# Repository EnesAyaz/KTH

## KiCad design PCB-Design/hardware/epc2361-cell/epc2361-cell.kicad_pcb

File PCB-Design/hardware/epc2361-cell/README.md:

# EPC2361 one-pair placement prototype

Open `epc2361-cell.kicad_pro` in KiCad 7. This is a native schematic and partially routed PCB placement study, not a fabrication release.

## Design basis

- One EPC2361 high-side device and one low-side device; eventual module has six of each.
- Bus: 75 V nominal and maximum. Switching: 50 kHz nominal, 100 kHz maximum.
- Eventual module: 220 A RMS AC. Ideal equal sharing gives 36.7 A RMS per cell and 51.9 A peak for a sinusoid. These are design targets, not demonstrated ratings.
- Study outline: 30 x 40 mm, four copper layers. Fabricator stackup and dielectric spacing are not selected.
- Four 1210 local ceramic sites. Candidate: TDK C3225X7R2A225K230AB, 2.2 uF / 100 V X7R each, 8.8 uF nominal total. Capacitance retained at 75 V, ripple heating and required count remain unqualified. External bulk DC link is needed.

## Placement and interfaces

QH1 and QL1 form a vertical pair, with local capacitors on the right and gate/source contacts on the left. Top copper combs connect the interleaved device pads; the filled first-inner DC-minus plane provides the proposed return path. Loop inductance has not been extracted or measured. The present narrow power traces illustrate topology and are not rated for the target current.

JGH1/JGL1: pin 1 gate input through RG1/RG2; pin 2 local source return. The source trace takes off at the source land nearest the gate. These are exposed contact pads, not a selected connector. The future driver board must preserve short gate/source paths. RG values are provisional; optional RGS1/RGS2 are DNP.

JDC1 = DC+, JDC2 = DC-, JAC1 = AC. Their 3 mm pads reserve interface positions; they are not rated sockets or final high-current terminals.

TP1 = high-side gate; TP2 = high-side source/AC; TP3 = low-side gate; TP4 = low-side source/DC-; TP5 = DC+; TP6 = DC-; TP7 = AC. Probe connections are still unrouted.

The drawing-layer rectangle reserves the MOSFET-top cold-plate contact corridor. An electrically insulating thermal interface is necessary between a common plate and the different source potentials. Cold plate, TIM, compression, mounting holes and thermal performance remain to be designed. Tall capacitors are outside the contact corridor, but the full cold-plate assembly has not been clearance checked.

## Verification and remaining work

KiCad successfully exported the schematic and both previews. The automated audit passes all 22 components and 44 pin-to-net assignments against the schematic manifest and PCB; footprint paths are linked to schematic UUIDs. Netlist labels carry KiCad's root-sheet slash prefix, normalized by the audit.

The latest native KiCad PCB DRC reports **0 geometric DRC violations, 13 unconnected items, and 0 footprint errors**. This is not a clean finished-board DRC: power ports, probes and optional gate resistors still need routing. Native schematic ERC has not been run. See `cell-drc.rpt` and `connectivity-check.txt`.

The project-local EPC2361 footprint transcribes the manufacturer's separate copper, mask and stencil geometries from datasheet revision 2.4, pages 11-12. Independent footprint/assembly sign-off is still required before fabrication; DRC does not validate the transcription against the datasheet.

Next engineering steps are footprint sign-off, selecting the stackup and real terminals, completing wide power distribution and probe routing, checking capacitance under bias, and electrothermal/commutation validation. Do not scale this cell by simply copying long shared gate traces. The six-cell board and gate-driver PCB are deferred.

## Reproducing the study

Run `scripts/build_cell_schematic.py`, then `scripts/build_cell_layout.py` with KiCad's bundled Python. Export a KiCad XML netlist to `cell-netlist.xml`, then run `scripts/check_cell.py` with KiCad Python. The latter fills zones, verifies connectivity and writes the DRC report. Generators overwrite their generated files; preserve manual edits first.

Reference review and system-level plan are in `../../docs/literature-review.md` and `../../docs/power-stage-plan.md`.

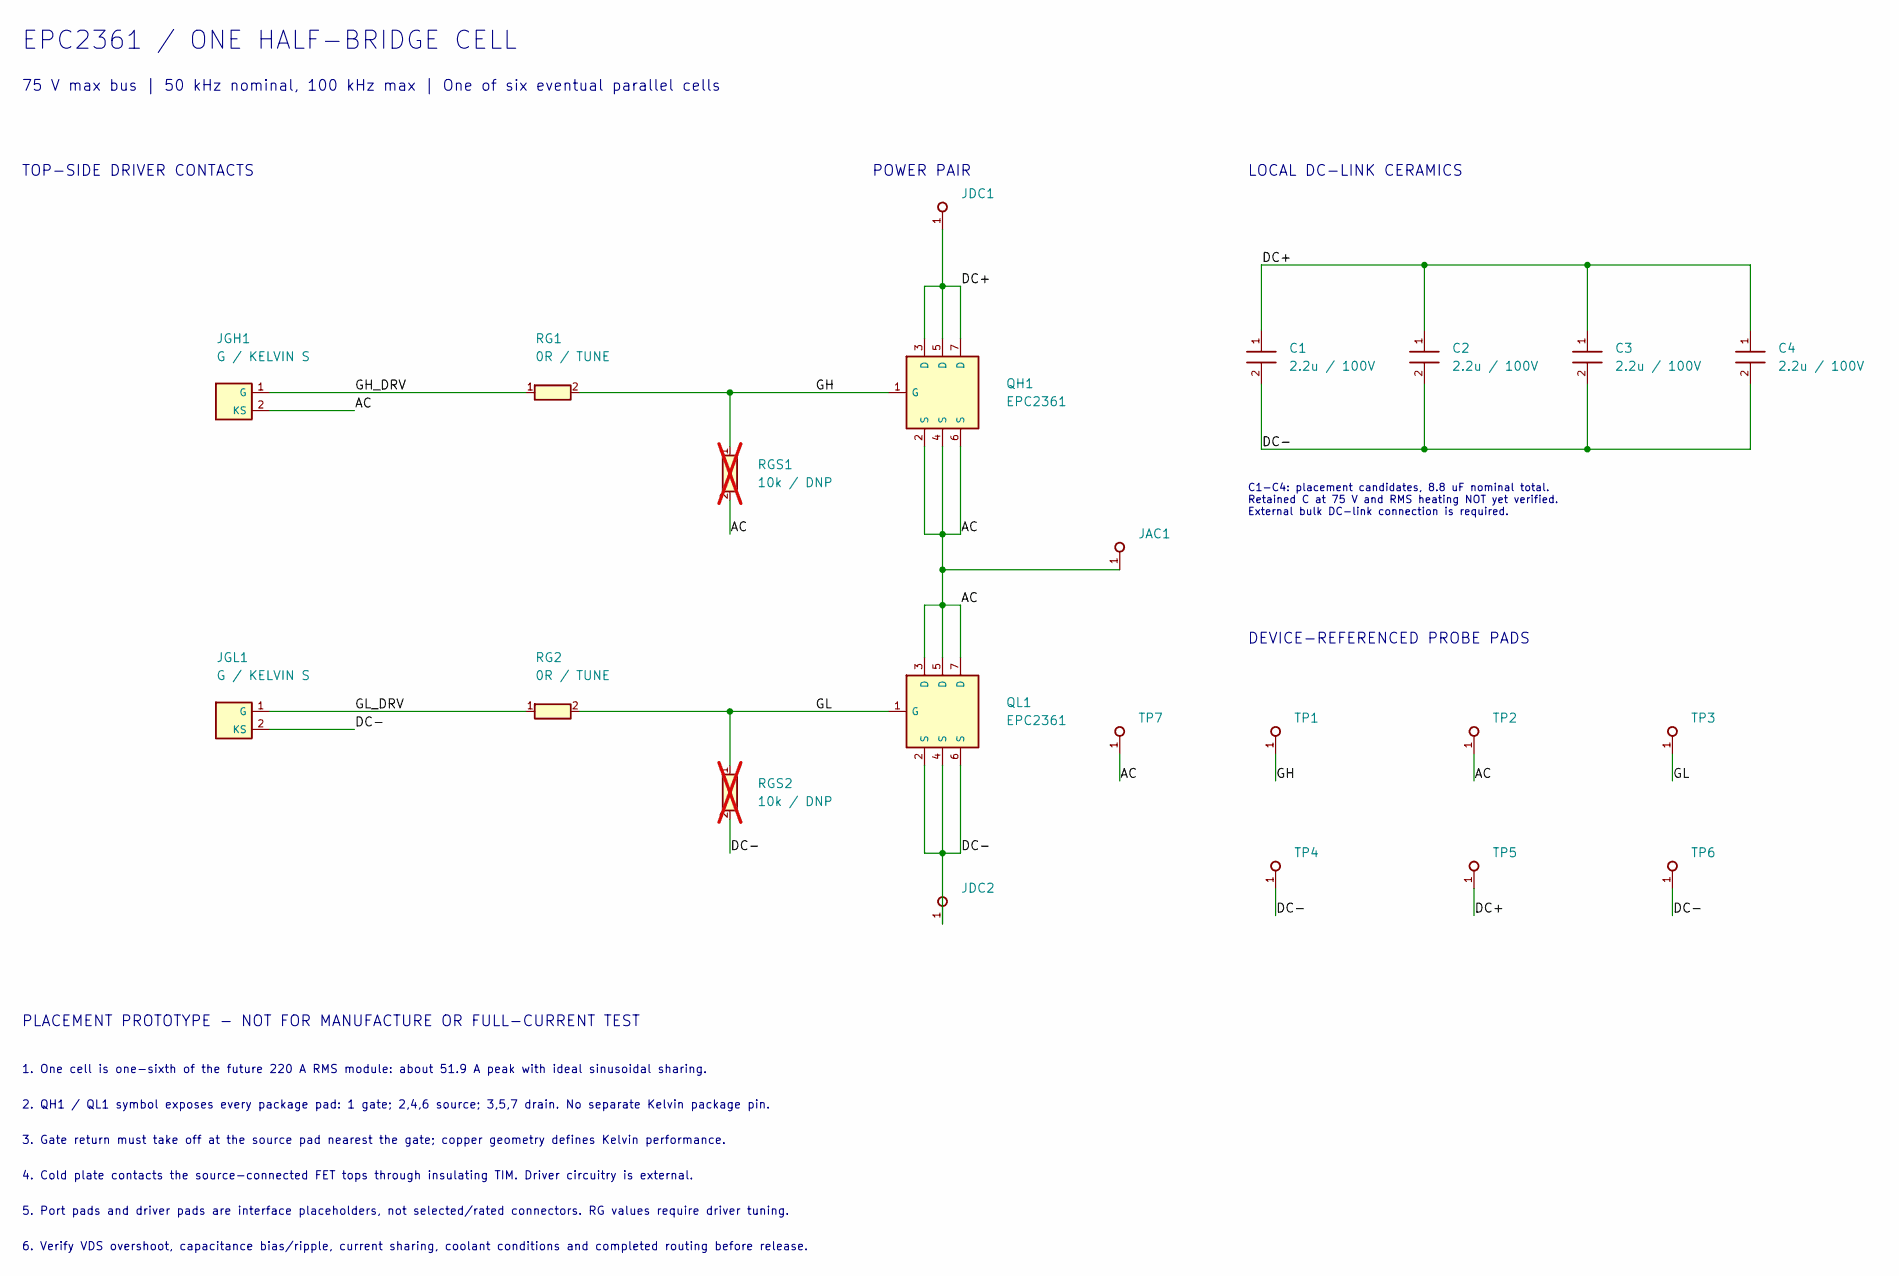
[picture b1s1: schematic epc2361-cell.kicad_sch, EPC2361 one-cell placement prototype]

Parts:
C1, C2, C3, C4: 2.2u / 100V; C_1210_3225Metric
JAC1: AC PORT PAD; Power_Port_Pad
JDC1: DC+ PORT PAD; Power_Port_Pad
JDC2: DC- PORT PAD; Power_Port_Pad
JGH1: G / KELVIN S; Gate_Source_Pads
JGL1: G / KELVIN S; Gate_Source_Pads
QH1: EPC2361
QL1: EPC2361
RG1, RG2: 0R / TUNE; R_0402_1005Metric
RGS1, RGS2: 10k / DNP; R_0402_1005Metric; not fitted
TP1: GH; Probe_Pad
TP2, TP7: AC; Probe_Pad
TP3: GL; Probe_Pad
TP4, TP6: DC-; Probe_Pad
TP5: DC+; Probe_Pad

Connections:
AC: JAC1.1, JGH1.2 (KS), QH1.2 (S), QH1.4 (S), QH1.6 (S), QL1.3 (D), QL1.5 (D), QL1.7 (D), RGS1.2, TP2.1, TP7.1
DC+: C1.1, C2.1, C3.1, C4.1, JDC1.1, QH1.3 (D), QH1.5 (D), QH1.7 (D), TP5.1
DC-: C1.2, C2.2, C3.2, C4.2, JDC2.1, JGL1.2 (KS), QL1.2 (S), QL1.4 (S), QL1.6 (S), RGS2.2, TP4.1, TP6.1
GH: QH1.1 (G), RG1.2, RGS1.1, TP1.1
GH_DRV: JGH1.1 (G), RG1.1
GL: QL1.1 (G), RG2.2, RGS2.1, TP3.1
GL_DRV: JGL1.1 (G), RG2.1

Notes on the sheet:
EPC2361 / ONE HALF-BRIDGE CELL
75 V max bus | 50 kHz nominal, 100 kHz max | One of six eventual parallel cells
TOP-SIDE DRIVER CONTACTS
POWER PAIR
LOCAL DC-LINK CERAMICS
C1-C4: placement candidates, 8.8 uF nominal total. Retained C at 75 V and RMS heating NOT yet verified. External bulk DC-link connection is required.
DEVICE-REFERENCED PROBE PADS
PLACEMENT PROTOTYPE - NOT FOR MANUFACTURE OR FULL-CURRENT TEST
1. One cell is one-sixth of the future 220 A RMS module: about 51.9 A peak with ideal sinusoidal sharing.
2. QH1 / QL1 symbol exposes every package pad: 1 gate; 2,4,6 source; 3,5,7 drain. No separate Kelvin package pin.
3. Gate return must take off at the source pad nearest the gate; copper geometry defines Kelvin performance.
4. Cold plate contacts the source-connected FET tops through insulating TIM. Driver circuitry is external.
5. Port pads and driver pads are interface placeholders, not selected/rated connectors. RG values require driver tuning.
6. Verify VDS overshoot, capacitance bias/ripple, current sharing, coolant conditions and completed routing before release.

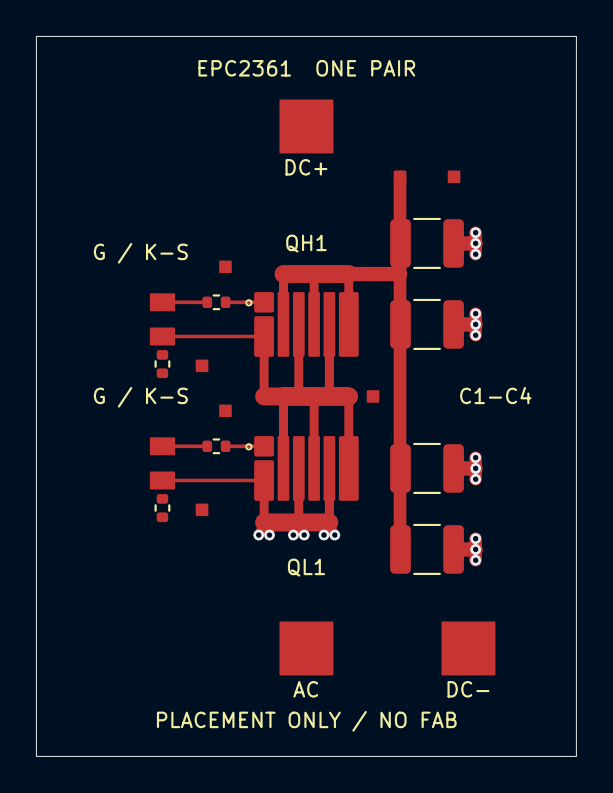
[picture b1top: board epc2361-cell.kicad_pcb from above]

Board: 4 copper layers, 30.0 x 40.0 mm, 22 parts (0 on the bottom side), 7 nets.

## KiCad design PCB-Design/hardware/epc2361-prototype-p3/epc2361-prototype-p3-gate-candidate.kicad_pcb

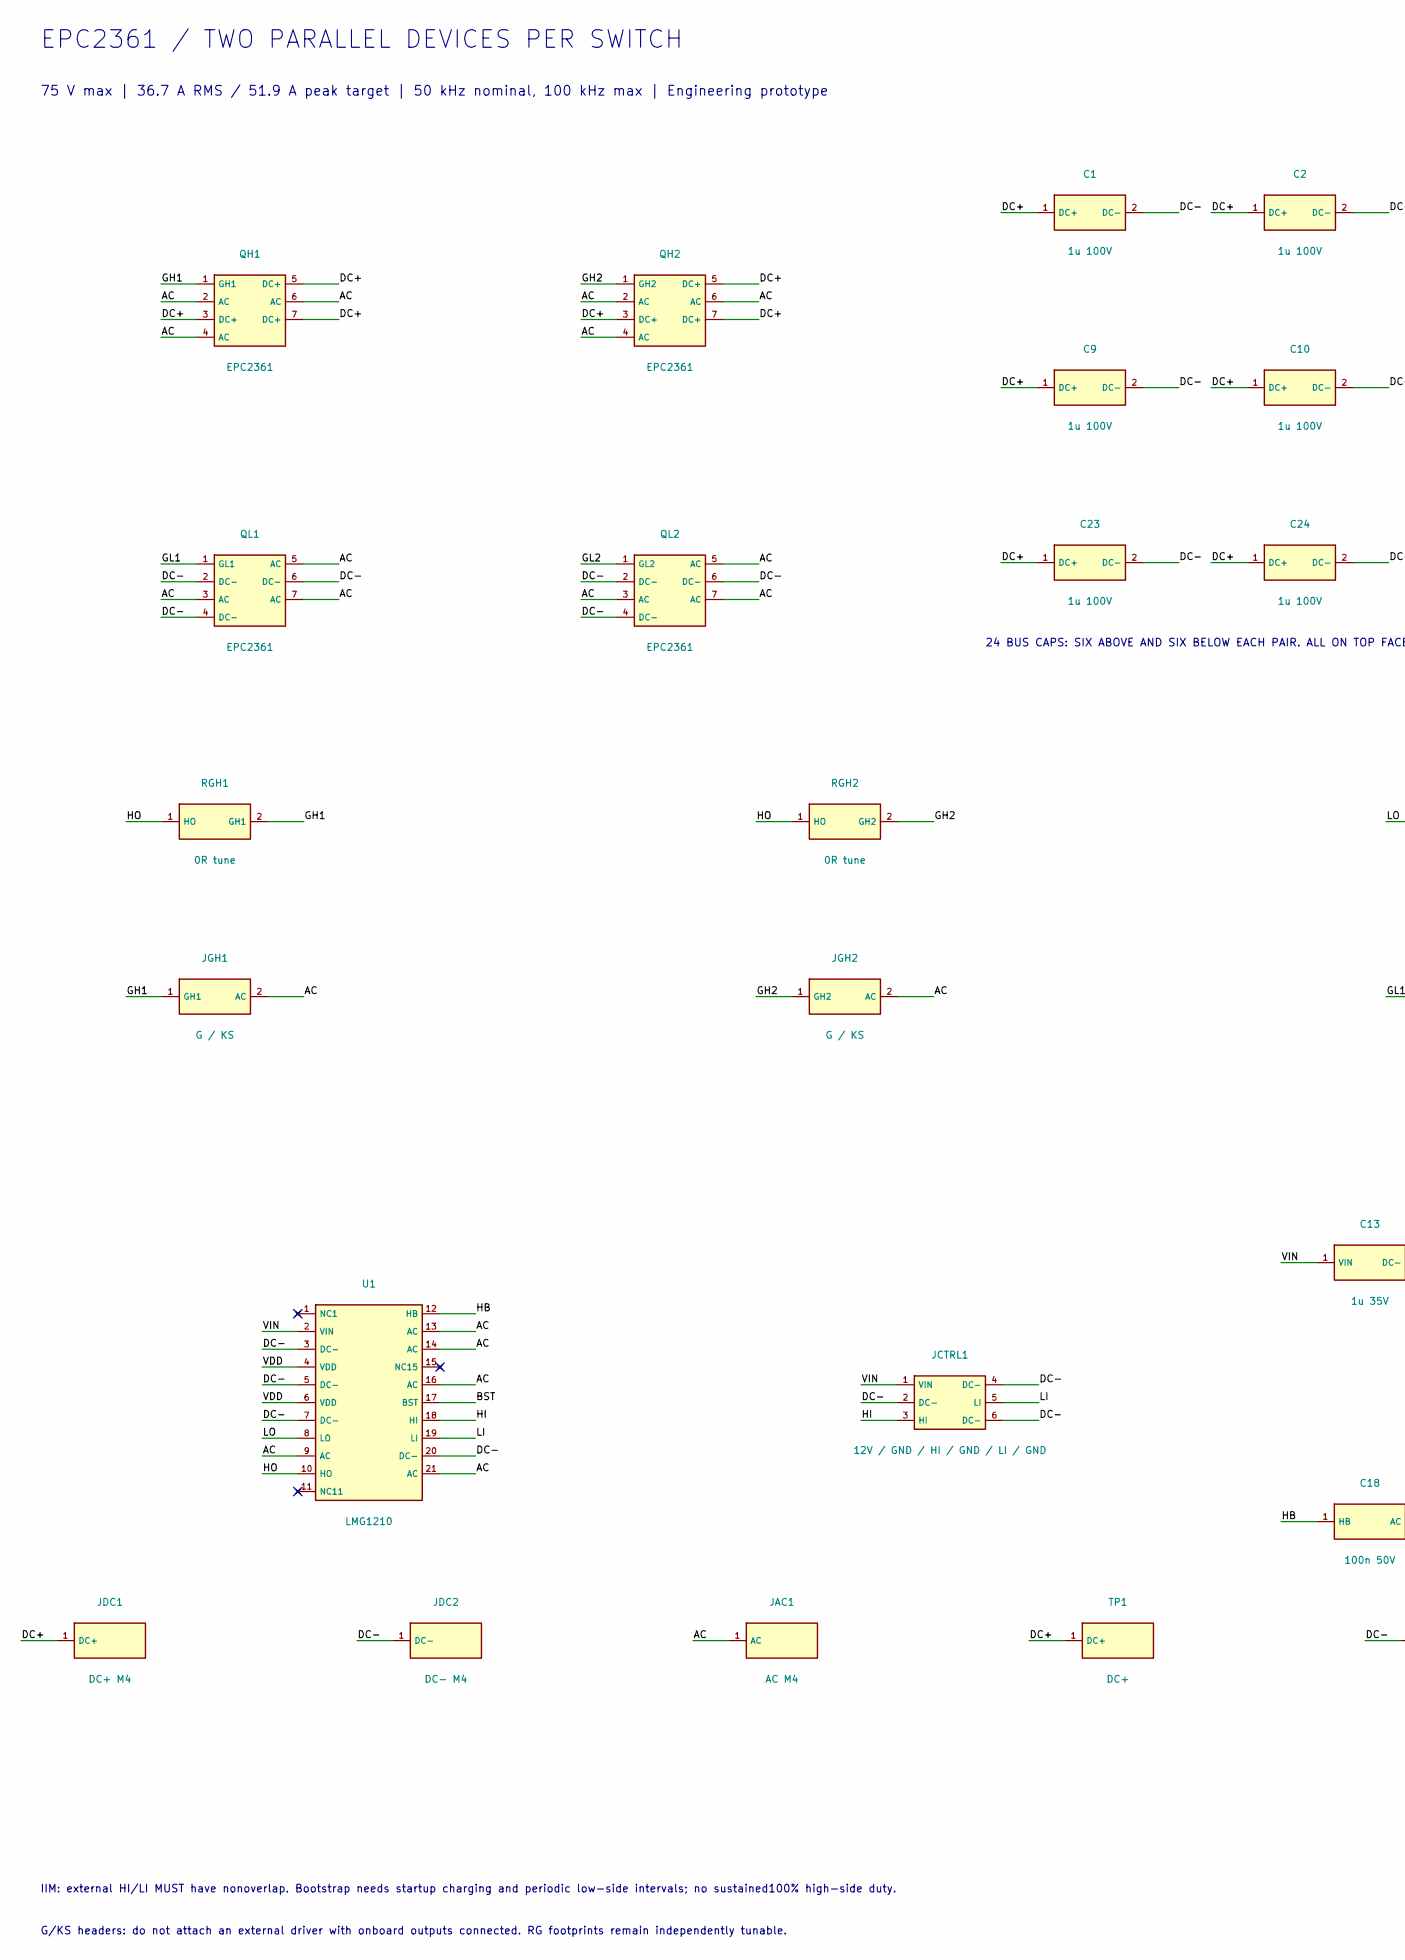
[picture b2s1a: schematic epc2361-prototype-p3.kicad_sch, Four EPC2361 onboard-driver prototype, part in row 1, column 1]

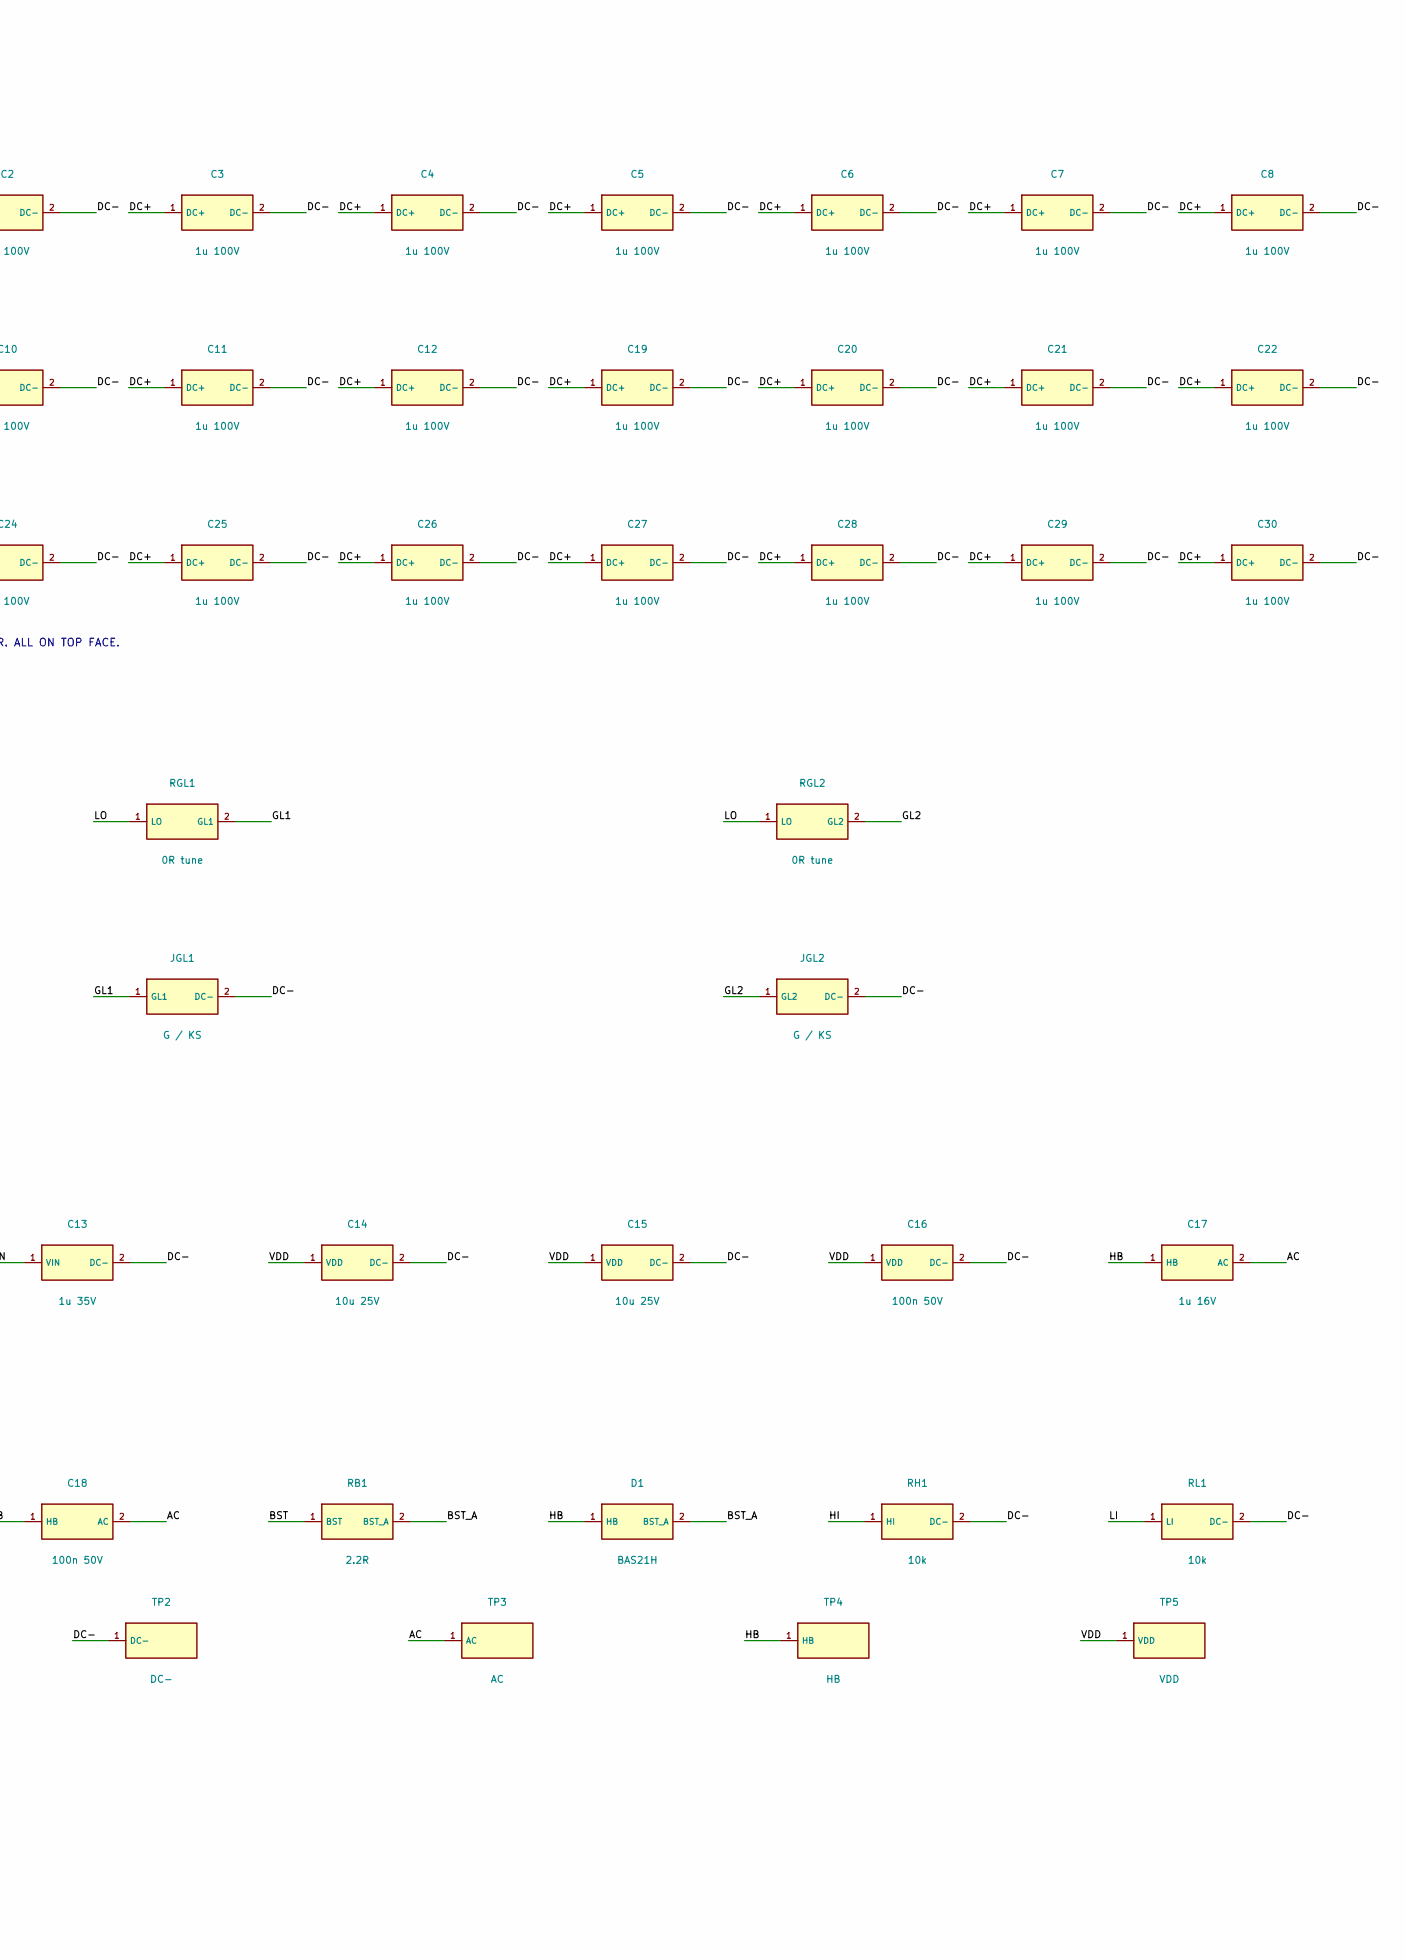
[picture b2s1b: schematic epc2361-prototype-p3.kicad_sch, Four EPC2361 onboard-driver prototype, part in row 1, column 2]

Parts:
C1, C2, C3, C4, C5, C6, C7, C8, C9, C10, C11, C12, C19, C20, C21, C22, C23, C24, C25, C26, C27, C28, C29, C30: 1u 100V; C_0805_2012Metric
C13: 1u 35V; C_0603_1608Metric
C14, C15: 10u 25V; C_0805_2012Metric
C16, C18: 100n 50V; C_0603_1608Metric
C17: 1u 16V; C_0603_1608Metric
D1: BAS21H; D_SOD-123F
JAC1: AC M4; Wuerth_REDCUBE-THR_WP-THRBU_74650094_THR
JCTRL1: 12V / GND / HI / GND / LI / GND; PinHeader_1x06_P2.54mm_Vertical
JDC1: DC+ M4; Wuerth_REDCUBE-THR_WP-THRBU_74650094_THR
JDC2: DC- M4; Wuerth_REDCUBE-THR_WP-THRBU_74650094_THR
JGH1, JGH2: G / KS; PinHeader_1x02_P1.27mm_Vertical
JGL1, JGL2: G / KS; PinHeader_1x02_P1.27mm_Vertical
QH1, QH2: EPC2361
QL1, QL2: EPC2361
RB1: 2.2R; R_0603_1608Metric
RGH1, RGH2: 0R tune; R_0402_1005Metric
RGL1, RGL2: 0R tune; R_0402_1005Metric
RH1: 10k; R_0402_1005Metric
RL1: 10k; R_0402_1005Metric
TP1: DC+; Probe_Pad
TP2: DC-; Probe_Pad
TP3: AC; Probe_Pad
TP4: HB; Probe_Pad
TP5: VDD; Probe_Pad
U1: LMG1210; LMG1210_RVR

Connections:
AC: C17.2 (AC), C18.2 (AC), JAC1.1, JGH1.2 (AC), JGH2.2 (AC), QH1.2 (AC), QH1.4 (AC), QH1.6 (AC), QH2.2 (AC), QH2.4 (AC), QH2.6 (AC), QL1.3 (AC), QL1.5 (AC), QL1.7 (AC), QL2.3 (AC), QL2.5 (AC), QL2.7 (AC), TP3.1, U1.9 (AC), U1.13 (AC), U1.14 (AC), U1.16 (AC), U1.21 (AC)
BST: RB1.1 (BST), U1.17 (BST)
BST_A: D1.2 (BST_A), RB1.2 (BST_A)
DC+: C1.1 (DC+), C2.1 (DC+), C3.1 (DC+), C4.1 (DC+), C5.1 (DC+), C6.1 (DC+), C7.1 (DC+), C8.1 (DC+), C9.1 (DC+), C10.1 (DC+), C11.1 (DC+), C12.1 (DC+), C19.1 (DC+), C20.1 (DC+), C21.1 (DC+), C22.1 (DC+), C23.1 (DC+), C24.1 (DC+), C25.1 (DC+), C26.1 (DC+), C27.1 (DC+), C28.1 (DC+), C29.1 (DC+), C30.1 (DC+), JDC1.1, QH1.3 (DC+), QH1.5 (DC+), QH1.7 (DC+), QH2.3 (DC+), QH2.5 (DC+), QH2.7 (DC+), TP1.1
DC-: C1.2 (DC-), C2.2 (DC-), C3.2 (DC-), C4.2 (DC-), C5.2 (DC-), C6.2 (DC-), C7.2 (DC-), C8.2 (DC-), C9.2 (DC-), C10.2 (DC-), C11.2 (DC-), C12.2 (DC-), C13.2 (DC-), C14.2 (DC-), C15.2 (DC-), C16.2 (DC-), C19.2 (DC-), C20.2 (DC-), C21.2 (DC-), C22.2 (DC-), C23.2 (DC-), C24.2 (DC-), C25.2 (DC-), C26.2 (DC-), C27.2 (DC-), C28.2 (DC-), C29.2 (DC-), C30.2 (DC-), JCTRL1.2 (DC-), JCTRL1.4 (DC-), JCTRL1.6 (DC-), JDC2.1, JGL1.2 (DC-), JGL2.2 (DC-), QL1.2 (DC-), QL1.4 (DC-), QL1.6 (DC-), QL2.2 (DC-), QL2.4 (DC-), QL2.6 (DC-), RH1.2 (DC-), RL1.2 (DC-), TP2.1, U1.3 (DC-), U1.5 (DC-), U1.7 (DC-), U1.20 (DC-)
GH1: JGH1.1 (GH1), QH1.1 (GH1), RGH1.2 (GH1)
GH2: JGH2.1 (GH2), QH2.1 (GH2), RGH2.2 (GH2)
GL1: JGL1.1 (GL1), QL1.1 (GL1), RGL1.2 (GL1)
GL2: JGL2.1 (GL2), QL2.1 (GL2), RGL2.2 (GL2)
HB: C17.1 (HB), C18.1 (HB), D1.1 (HB), TP4.1, U1.12 (HB)
HI: JCTRL1.3 (HI), RH1.1 (HI), U1.18 (HI)
HO: RGH1.1 (HO), RGH2.1 (HO), U1.10 (HO)
LI: JCTRL1.5 (LI), RL1.1 (LI), U1.19 (LI)
LO: RGL1.1 (LO), RGL2.1 (LO), U1.8 (LO)
NC1: U1.1 (NC1)
NC11: U1.11 (NC11)
NC15: U1.15 (NC15)
VDD: C14.1 (VDD), C15.1 (VDD), C16.1 (VDD), TP5.1, U1.4 (VDD), U1.6 (VDD)
VIN: C13.1 (VIN), JCTRL1.1 (VIN), U1.2 (VIN)

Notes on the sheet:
EPC2361 / TWO PARALLEL DEVICES PER SWITCH
75 V max | 36.7 A RMS / 51.9 A peak target | 50 kHz nominal, 100 kHz max | Engineering prototype
24 BUS CAPS: SIX ABOVE AND SIX BELOW EACH PAIR. ALL ON TOP FACE.
IIM: external HI/LI MUST have nonoverlap. Bootstrap needs startup charging and periodic low-side intervals; no sustained100% high-side duty.
G/KS headers: do not attach an external driver with onboard outputs connected. RG footprints remain independently tunable.

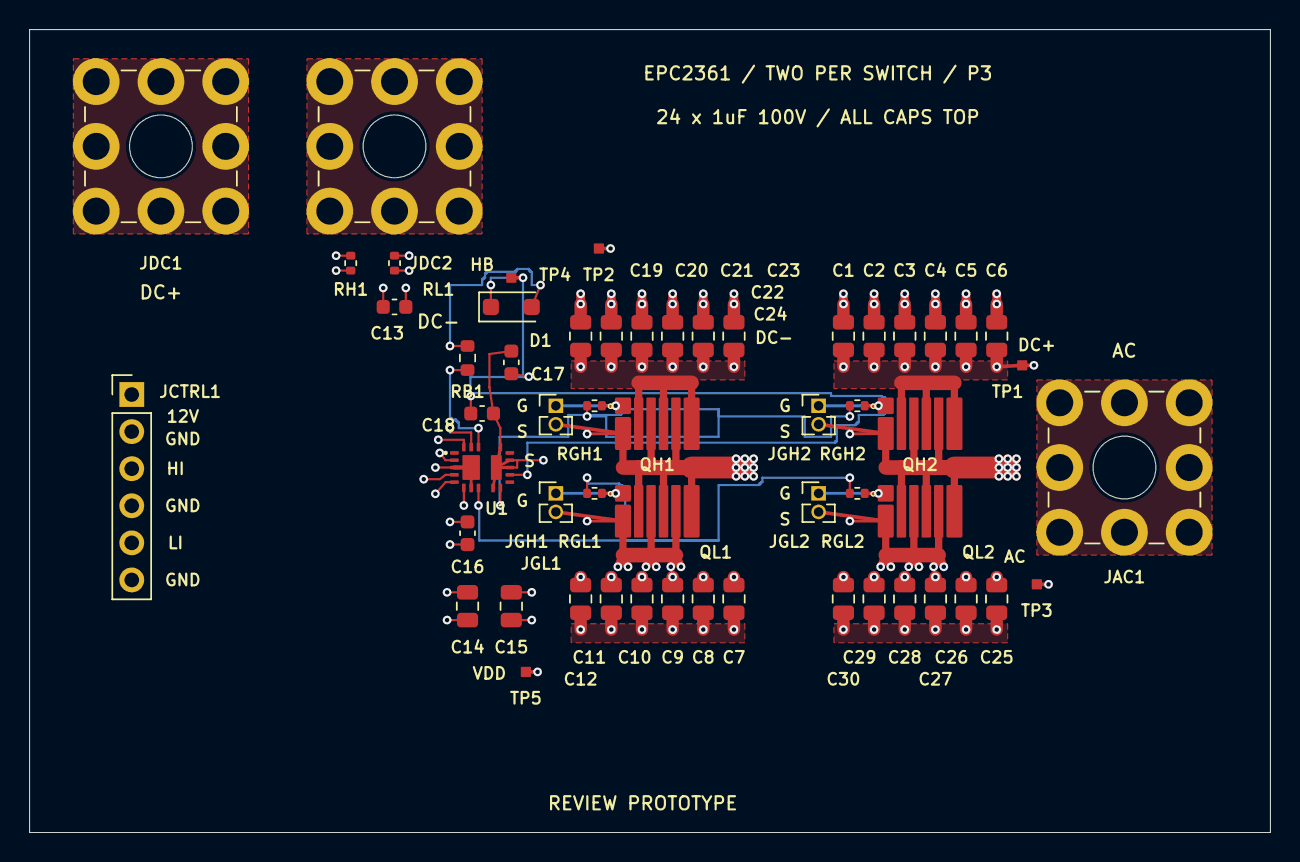
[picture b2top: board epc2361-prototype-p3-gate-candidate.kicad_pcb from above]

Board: 4 copper layers, 85.0 x 55.0 mm, 56 parts (0 on the bottom side), 16 nets.

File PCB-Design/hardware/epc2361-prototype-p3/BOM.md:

# Prototype BOM

All quantities are for one four-FET board. Provisional engineering BOM; not purchasing release.

| References | Qty | MPN | Value | Footprint | Fit | Notes |
|---|---:|---|---|---|---|---|
| QH1, QL1, QH2, QL2 | 4 | EPC2361 | EPC2361 | epc2361-prototype:EPC2361 | Fit |  |
| C1, C2, C3, C4, C5, C6, C7, C8, C9, C10, C11, C12, C19, C25, C20, C26, C21, C27, C22, C28, C23, C29, C24, C30 | 24 | C2012X7S2A105K125AB | 1u 100V | Capacitor_SMD:C_0805_2012Metric | Fit |  |
| RGH1, RGL1, RGH2, RGL2 | 4 | RC0402JR-070RL | 0R tune | Resistor_SMD:R_0402_1005Metric | Fit | Individual gate damping footprint. Tune during double-pulse testing. |
| JGH1, JGL1, JGH2, JGL2 | 4 | FTS-102-01-L-S | G / KS | Connector_PinHeader_1.27mm:PinHeader_1x02_P1.27mm_Vertical | Fit | Measurement/external-drive header; never connect a second active driver. Remove local series resistor to isolate onboard output. Generic footprint: verify manufacturer drawing before release. |
| JDC1 | 1 | 74650094 | DC+ M4 | TerminalBlock_Wuerth:Wuerth_REDCUBE-THR_WP-THRBU_74650094_THR | Fit | 85 A maximum at20C is terminal-only; assembly/current path requires validation. 1.2Nm maximum specified torque. |
| JDC2 | 1 | 74650094 | DC- M4 | TerminalBlock_Wuerth:Wuerth_REDCUBE-THR_WP-THRBU_74650094_THR | Fit | 85 A maximum at20C is terminal-only; assembly/current path requires validation. 1.2Nm maximum specified torque. |
| JAC1 | 1 | 74650094 | AC M4 | TerminalBlock_Wuerth:Wuerth_REDCUBE-THR_WP-THRBU_74650094_THR | Fit | 85 A maximum at20C is terminal-only; assembly/current path requires validation. 1.2Nm maximum specified torque. |
| U1 | 1 | LMG1210RVRR | LMG1210 | epc2361-prototype:LMG1210_RVR | Fit | IIM: external nonoverlapping HI/LI; no internal shoot-through interlock in this mode. |
| JCTRL1 | 1 | TSW-106-07-G-S | 12V / GND / HI / GND / LI / GND | Connector_PinHeader_2.54mm:PinHeader_1x06_P2.54mm_Vertical | Fit |  |
| C13 | 1 | C1608X7R1V105K080AC | 1u 35V | Capacitor_SMD:C_0603_1608Metric | Fit | Verify effective capacitance and temperature; VDD X5R parts rated85C. |
| C14, C15 | 2 | C2012X5R1E106K125AB | 10u 25V | Capacitor_SMD:C_0805_2012Metric | Fit | Verify effective capacitance and temperature; VDD X5R parts rated85C. |
| C16, C18 | 2 | C1608X7R1H104K080AA | 100n 50V | Capacitor_SMD:C_0603_1608Metric | Fit | Verify effective capacitance and temperature; VDD X5R parts rated85C. |
| C17 | 1 | C1608X7R1C105K080AC | 1u 16V | Capacitor_SMD:C_0603_1608Metric | Fit | Verify effective capacitance and temperature; VDD X5R parts rated85C. |
| RB1 | 1 | RC0603FR-072R2L | 2.2R | Resistor_SMD:R_0603_1608Metric | Fit |  |
| D1 | 1 | BAS21H,115 | BAS21H | Diode_SMD:D_SOD-123F | Fit | External bootstrap diode: cathode HB, anode BST_A. Not a bootstrap voltage clamp. |
| RH1, RL1 | 2 | RC0402FR-0710KL | 10k | Resistor_SMD:R_0402_1005Metric | Fit |  |
| TP1 | 1 | PCB copper test pad | DC+ | epc2361-prototype:Probe_Pad | Fit | PCB feature; no purchased component. |
| TP2 | 1 | PCB copper test pad | DC- | epc2361-prototype:Probe_Pad | Fit | PCB feature; no purchased component. |
| TP3 | 1 | PCB copper test pad | AC | epc2361-prototype:Probe_Pad | Fit | PCB feature; no purchased component. |
| TP4 | 1 | PCB copper test pad | HB | epc2361-prototype:Probe_Pad | Fit | PCB feature; no purchased component. |
| TP5 | 1 | PCB copper test pad | VDD | epc2361-prototype:Probe_Pad | Fit | PCB feature; no purchased component. |
